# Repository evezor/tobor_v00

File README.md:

# tobor_v00
Tobor (robot spelled backwards), was built to be the most versatile open-source robotics system

Find out more about this project, additional source files will be released [here](https://www.crowdsupply.com/evezor-inc/tobor-robotics-and-automation-platform)

Tobor Robot Arm Features

* ESP32 microcontroller with 4 MB SPIRAM
    * Runs Micropython
* 3 DRV8825 stepper motor drivers
* 2 AS5048B 14-bit absolute encoders
    * Allows for low/no motion homing
    * Collaborative programming
* 8 position addressable LED ring
    * Can be used to display states of motors or the machine
* External stepper driver and peripheral port
* CNC controller powered by Fluid NC with dedicated FTDI and reset switch
* Micro-SD card slot
* WiFi enabled
* CANbus Edge Board Interface
* Servo header
* 24 VDC power input
* 1 user programmable tactile button
* Reset button
* FTDI port
* Edgeboard standards
    * Heartbeat LED
    * Function button
    * Status addressable LED

Find out more about this project, additional source files will be released [here](https://www.crowdsupply.com/evezor-inc/tobor-robotics-and-automation-platform)

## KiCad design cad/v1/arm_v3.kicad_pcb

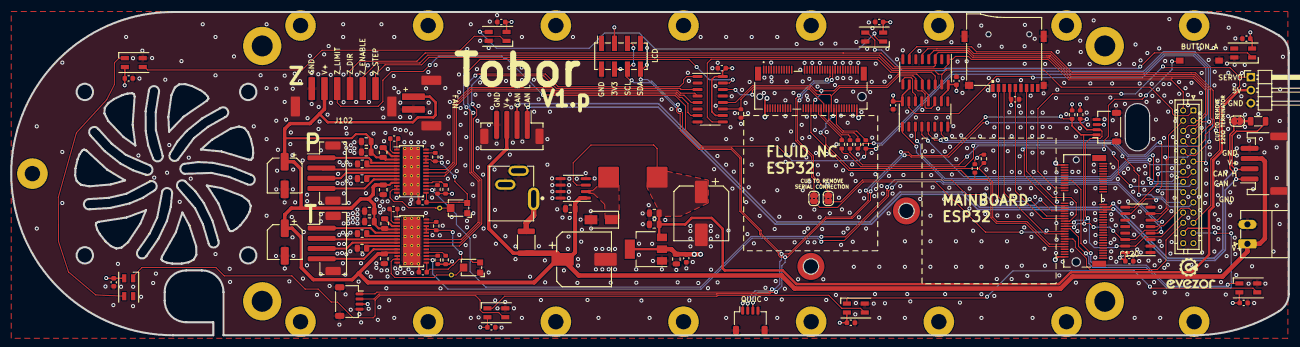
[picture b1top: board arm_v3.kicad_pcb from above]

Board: 4 copper layers, 250.2 x 63.3 mm, 121 parts (0 on the bottom side), 98 nets.

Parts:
C101, C102, C103, C104, C105, C106, C107, C108, C114, C116, C117, C118, C119, C120: .1uF; C_0603_1608Metric
C109, C111: 220uF; CP_Elec_10x10.5
C110, C112, C205, C305: 4.7uF 50V; C_0805_2012Metric
C113, C115: 22uF; C_0805_2012Metric
C201, C301: 10 nF; C_0603_1608Metric
C202, C302: 0.47uF; C_0603_1608Metric
C203, C206, C207, C303, C306, C307: .1uF 100V; C_0805_2012Metric
C204, C304: 47uF; CP_Elec_6.3x7.7
D101, D102, D103, D104, D105, D106, D107, D108: SK6812MINI; LED_SK6812MINI_PLCC4_3.5x3.5mm_P1.75mm
D109: SX35_SCHOTTKY; D_SMA
F101: Polyfuse_Small; Fuse_1812_4532Metric
H101, H102, H103, H104: MountingHole; MountingHole_4.1mm_M4_DIN965_Pad
H105, H106, H107, H108, H109, H110, H111, H112, H113, H114, H115, H116, H117, H118, H119, H120, H121: MountingHole; MountingHole_3mm_Pad
H122, H123: MountingHole; Mounting_Wuerth_WA-SMSI-M2_H2.5mm_9774025243
J101: Conn_01x03; PhoenixContact_MC_1,5_2-G-3.81_1x02_P3.81mm_Horizontal
J102: Conn_01x06_MountingPin; CONN_JST_XH_6_VERTICAL
J103: fan; JST_XH_2_VERTICAL
J104: Conn_01x03; PinHeader_1x03_P2.54mm_Horizontal
J105: Conn_02x04_Odd_Even; PinSocket_2x04_P2.54mm_Vertical_SMD
J106, J108, J110: Conn_01x04_MountingPin; JST_SH_SM04B-SRSS-TB_1x04-1MP_P1.00mm_Horizontal
J107: Barrel_Jack_Switch; Vertical_barrel
J109: Conn_02x10_Odd_Even; JST_PHD_B28B-PHDSS_2x14_P2.00mm_Vertical
J111: Micro_SD_Card_Det; Conn_uSDcard
J112: Conn_01x04; JST_PH_S4B-PH-SM4-TB_1x04-1MP_P2.00mm_Horizontal
J113: Conn_01x02; JST_PH_B4B-PH-SM4-TB_1x04-1MP_P2.00mm_Vertical
J114, J115: Bus_M.2_Socket_E_ESP32; AMPHENOL_MDT420E02002
J201, J301: Conn_01x04_MountingPin; JST_PH_B4B-PH-SM4-TB_1x04-1MP_P2.00mm_Vertical
JP101, JP102: SolderJumper_2_Bridged; SolderJumper-2_P1.3mm_Bridged2Bar_RoundedPad1.0x1.5mm
JP103: can_jumper; SolderJumper-2_P1.3mm_Bridged2Bar_RoundedPad1.0x1.5mm
L101: 68uF; INDUCTOR-68uH
R101, R102: 4.7k; R_0603_1608Metric
R103: 120R; R_1206_3216Metric
R104, R105, R106, R202, R203, R302, R303: 10k; R_0603_1608Metric
R107, R108, R109, R110: 220R; R_0603_1608Metric
R201, R301: 1.5k; R_0603_1608Metric
R204, R205, R304, R305: 0.1R; R_0805_2012Metric
RV201, RV301: 10k POT; Potentiometer_Bourns_TC33X_Vertical
SW101: SW_Push; SWITCH_2x3_SMD_TACTILE_GREEN
TP201, TP301: TestPoint; TestPoint_THTPad_D1.0mm_Drill0.5mm
U101: XL1509; SOIC-8_3.9x4.9mm_P1.27mm
U102: AMS1117-3.3; SOT-223-3_TabPin2
U103, U104, U105: 74AHCT595; SOIC-16_3.9x9.9mm_P1.27mm
U106: PCF8574; SOIC-16_3.9x9.9mm_P1.27mm
U201, U301: DRV8825PWPR; HTSSOP-28-1EP_4.4x9.7mm_P0.65mm_EP3.4x9.5mm_ThermalVias

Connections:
+3V3: C101.2, C102.2, C103.2, C104.2, C105.2, C106.2, C107.2, C108.2, C114.1, C115.1, C116.1, C117.2, C118.2, C119.2, C120.1, D101.4 (VDD), D102.4 (VDD), D103.4 (VDD), D104.4 (VDD), D105.4 (VDD), D106.4 (VDD), D107.4 (VDD), D108.4 (VDD), J105.3, J105.4, J106.3, J108.3, J109.27, J110.3, J111.4 (VDD), J114.2 (3.3V), J114.74 (3.3V), J115.2 (3.3V), J115.74 (3.3V), R101.1, R102.1, R104.2, R106.2, R201.2, R203.2, R301.2, R303.2, U102.2 (VO), U103.10 (~SRCLR), U103.16 (VCC), U104.10 (~SRCLR), U104.16 (VCC), U105.10 (~SRCLR), U105.16 (VCC), U106.16 (VDD)
+5V: C111.1, C112.1, C113.1, J104.2, J109.26, L101.1, U101.3 (FEEDBACK), U102.3 (VI)
+VDC: C109.1, C110.1, C203.1, C204.1, C205.1, C206.2, C207.2, C303.1, C304.1, C305.1, C306.2, C307.2, F101.1, J101.1, J102.5, J103.1, J112.3, J113.3, U101.1 (VIN), U201.4 (VMA), U201.11 (VMB), U301.4 (VMA), U301.11 (VMB)
/A_DIR: J109.8, U104.7 (QH)
/A_ENABLE: J109.7, U104.5 (QF)
/A_LIMIT: J109.10, R108.1
/A_RESET: J109.9, U106.7 (P3)
/A_STEP: J109.6, U104.4 (QE)
/BUTTON A: J114.34, SW101.1
/B_DIR: J109.13, U105.3 (QD)
/B_ENABLE: J109.12, U105.1 (QB)
/B_LIMIT: J109.15, R109.1
/B_RESET: J109.14, U106.9 (P4)
/B_STEP: J109.11, U105.15 (QA)
/CAN_H: J112.2, J113.2, J114.35 (CAN_H), R103.2
/CAN_L: J112.1, J113.1, J114.37 (CAN_L), JP103.2 (B)
/C_DIR: J109.18, U105.7 (QH)
/C_ENABLE: J109.17, U105.5 (QF)
/C_LIMIT: J109.20, R110.1
/C_RESET: J109.19, U106.10 (P5)
/C_STEP: J109.16, U105.4 (QE)
/GRBL_PROBE: J114.66, J115.38, R104.1
/GRBL_RX: J114.38, JP102.2 (B)
/GRBL_RXD0: J115.53 (UART_RX), JP101.1 (A)
/GRBL_TX: J114.54, JP101.2 (B)
/GRBL_TXDO: J115.55 (UART_TX), JP102.1 (A)
/HOLD: J114.64, J115.56, R106.1
/I2S_CLK: J115.54, R105.2, U103.11 (SRCLK), U104.11 (SRCLK), U105.11 (SRCLK)
/I2S_DATA: J115.48, U103.14 (SER)
/I2S_WS: J115.40, U103.12 (RCLK), U104.12 (RCLK), U105.12 (RCLK)
/NEO_RING: D101.3 (DIN), J114.14
/P25: J109.25, J114.52
/P60: J109.24, J114.60
/PHI_STEPPER/3VP: C302.1, R302.2, RV301.3, U301.15 (V3P3OUT), U301.24 (MODE0), U301.25 (MODE1), U301.26 (MODE2)
/SCK: J111.5 (CLK), J114.44
/SCL: J105.5, J105.6, J106.1, J108.1, J109.21, J110.1, J114.50, R101.2, U106.14 (SCL)
/SDA: J105.7, J105.8, J106.2, J108.2, J109.22, J110.2, J114.48, R102.2, U106.15 (SDA)
/SD_CS: J111.2 (DAT3/CD), J114.42
/SD_MISO: J111.7 (DAT0), J114.46
/SD_MOSI: J111.3 (CMD), J114.56
/SERVO: J104.1, J109.23, J114.20
/THETA_STEPPER/3VP: C202.1, R202.2, RV201.3, U201.15 (V3P3OUT), U201.24 (MODE0), U201.25 (MODE1), U201.26 (MODE2)
/Z_DIR: J102.3, J109.3, U104.3 (QD)
/Z_ENABLE: J102.2, J109.2, U104.1 (QB)
/Z_LIMIT: J102.4, J109.5, R107.1
/Z_RESET: J109.4, U106.6 (P2)
/Z_STEP: J102.1, J109.1, U104.15 (QA)
GND: C101.1, C102.1, C103.1, C104.1, C105.1, C106.1, C107.1, C108.1, C109.2, C110.2, C111.2, C112.2, C113.2, C114.2, C115.2, C116.2, C117.1, C118.1, C119.1, C120.2, C202.2, C204.2, C205.2, C206.1, C207.1, C302.2, C304.2, C305.2, C306.1, C307.1, D101.2 (VSS), D102.2 (VSS), D103.2 (VSS), D105.2 (VSS), D106.2 (VSS), D107.2 (VSS), D108.2 (VSS), D109.2 (A), J101.2, J102.6, J102.MP (MountPin), J103.2, J103.MP (MountPin), J104.3, J105.1, J105.2, J106.4, J106.MP (MountPin), J107.2, J107.3, J108.4, J108.MP (MountPin), J109.28, J110.4, J110.MP (MountPin), J111.6 (VSS), J111.11 (SHIELD), J112.4, J112.MP (MountPin), J113.4, J113.MP (MountPin), J114.1 (GND), J114.7 (GND), J114.18 (GND), J114.33 (GND), J114.36 (GND), J114.39 (GND), J114.45 (GND), J114.57 (GND), J114.63 (GND), J114.69 (GND), J114.75 (GND), J115.1 (GND), J115.7 (GND), J115.18 (GND), J115.33 (GND), J115.36 (GND), J115.39 (GND), J115.45 (GND), J115.57 (GND), J115.63 (GND), J115.69 (GND), J115.75 (GND), J201.MP (MountPin), J301.MP (MountPin), R105.1, R204.1, R205.1, R304.1, R305.1, RV201.1, RV301.1, SW101.2, U101.4 (ON/OFF), U101.5 (GND), U101.6 (GND), U101.7 (GND), U101.8 (GND), U102.1 (GND), U103.8 (GND), U103.13 (~OE), U104.8 (GND), U104.13 (~OE), U105.8 (GND), U105.13 (~OE), U106.1 (A0), U106.2 (A1), U106.3 (A2), U106.8 (VSS), U201.14 (GND), U201.28 (GND), U201.29 (GND), U301.14 (GND), U301.28 (GND), U301.29 (GND)
unnamed: D101.1 (DOUT), D102.3 (DIN)
unnamed: D102.1 (DOUT), D103.3 (DIN)
unnamed: D103.1 (DOUT), D104.3 (DIN)
unnamed: D104.1 (DOUT), D105.3 (DIN)
unnamed: D105.1 (DOUT), D106.3 (DIN)
unnamed: D106.1 (DOUT), D107.3 (DIN)
unnamed: D107.1 (DOUT), D108.3 (DIN)
unnamed: D109.1 (K), L101.2, U101.2 (OUTPUT)
unnamed: F101.2, J107.1
unnamed: J115.44, R110.2
unnamed: J115.46, R109.2
unnamed: J115.52, R108.2
unnamed: J115.58, R107.2
unnamed: J201.1, U201.5 (AOUT1)
unnamed: J201.2, U201.7 (AOUT2)
unnamed: J201.3, U201.8 (BOUT2)
unnamed: J201.4, U201.10 (BOUT1)
unnamed: J301.1, U301.5 (AOUT1)
unnamed: J301.2, U301.7 (AOUT2)
unnamed: J301.3, U301.8 (BOUT2)
unnamed: J301.4, U301.10 (BOUT1)
unnamed: JP103.1 (A), R103.1
unnamed: U103.9 (QH'), U104.14 (SER)
unnamed: U104.9 (QH'), U105.14 (SER)
unnamed: R201.1, U201.18 (!FAULT)
unnamed: R202.1, U201.27 (!HOME)
unnamed: R203.1, U201.17 (!SLEEP)
unnamed: RV201.2, TP201.1, U201.12 (AVREF), U201.13 (BVREF)
unnamed: C201.1, U201.1 (CP1)
unnamed: C201.2, U201.2 (CP2)
unnamed: R205.2, U201.6 (ISENA)
unnamed: R204.2, U201.9 (ISENB)
unnamed: C203.2, U201.3 (VCP)
unnamed: R301.1, U301.18 (!FAULT)
unnamed: R302.1, U301.27 (!HOME)
unnamed: R303.1, U301.17 (!SLEEP)
unnamed: RV301.2, TP301.1, U301.12 (AVREF), U301.13 (BVREF)
unnamed: C301.1, U301.1 (CP1)
unnamed: C301.2, U301.2 (CP2)
unnamed: R305.2, U301.6 (ISENA)
unnamed: R304.2, U301.9 (ISENB)
unnamed: C303.2, U301.3 (VCP)
PHI_DIR: U103.7 (QH), U301.20 (DIR)
PHI_ENABLE: U103.5 (QF), U301.21 (!ENBL)
PHI_RESET: U106.5 (P1), U301.16 (!RESET)
PHI_STEP: U103.4 (QE), U301.22 (STEP)
THETA_DIR: U103.3 (QD), U201.20 (DIR)
THETA_ENABLE: U103.1 (QB), U201.21 (!ENBL)
THETA_RESET: U106.4 (P0), U201.16 (!RESET)
THETA_STEP: U103.15 (QA), U201.22 (STEP)

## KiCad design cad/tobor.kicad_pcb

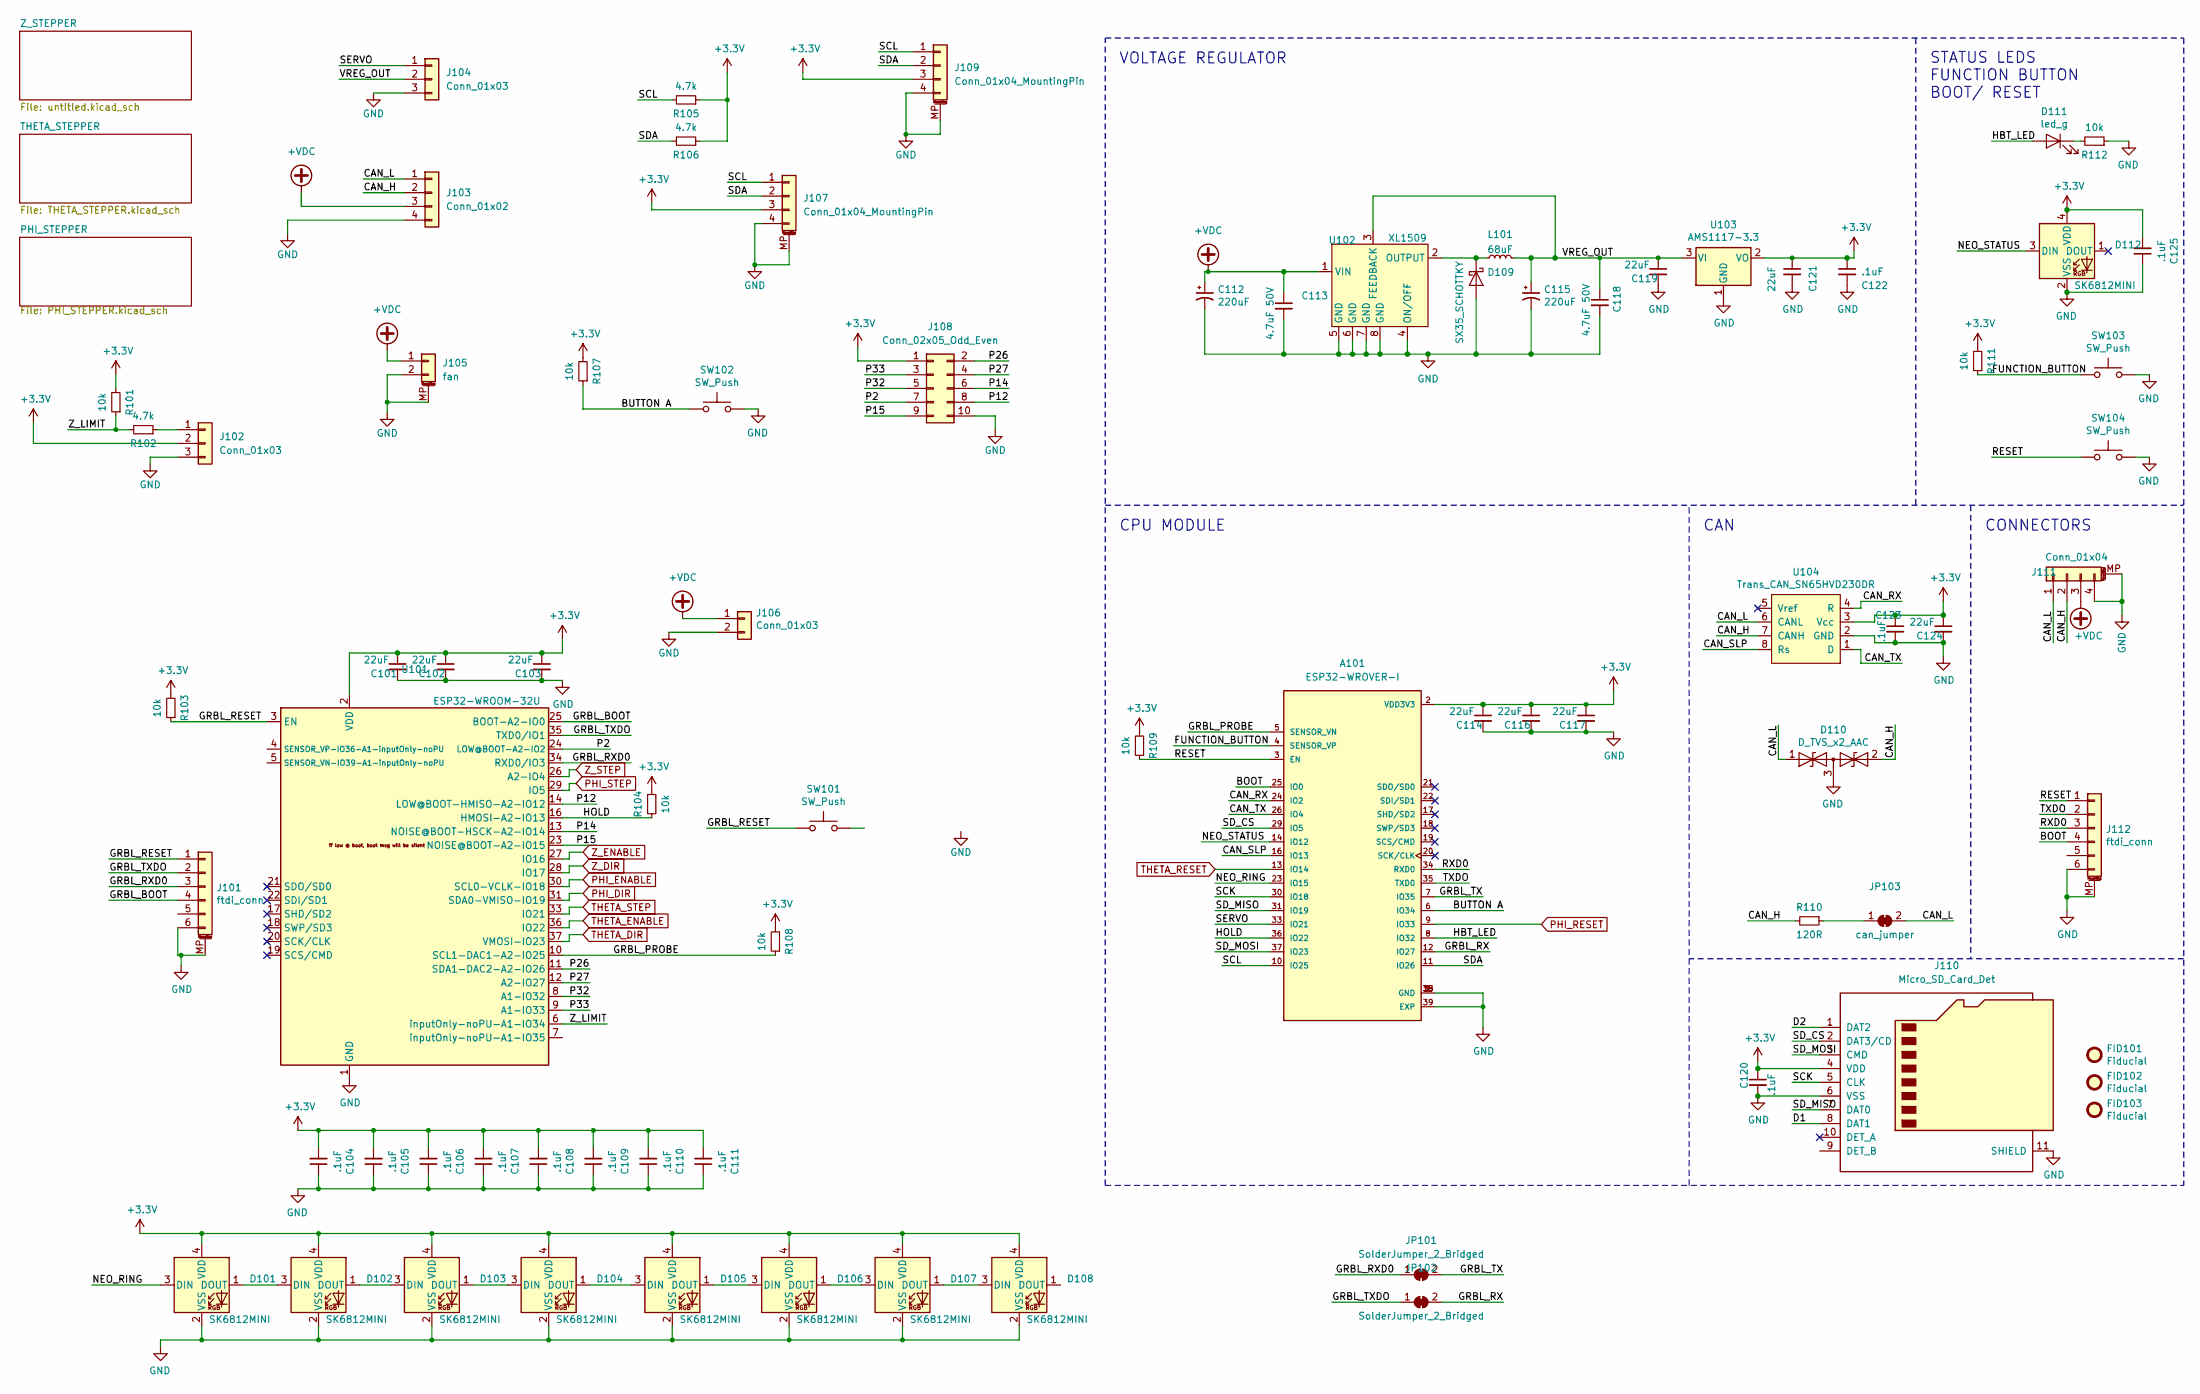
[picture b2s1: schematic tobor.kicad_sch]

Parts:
A101: ESP32-WROVER-I; XCVR_ESP32-WROVER-I; DIGI-KEY_PART_NUMBER 1904-1008-1-ND
C101, C102, C103, C114, C116, C117, C119, C121, C124: 22uF; C_0805_2012Metric
C104, C105, C106, C107, C108, C109, C110, C111, C120, C122, C123, C125: .1uF; C_0603_1608Metric
C112, C115: 220uF; CP_Elec_10x10.5
C113, C118: 4.7uF 50V; C_0805_2012Metric
D101, D102, D103, D104, D105, D106, D107, D108, D112: SK6812MINI; LED_SK6812MINI_PLCC4_3.5x3.5mm_P1.75mm
D109: SX35_SCHOTTKY; D_SMA
D110: D_TVS_x2_AAC; SOT-23
D111: led_g; LED_0603_1608Metric
FID101, FID102, FID103: Fiducial; Fiducial_0.5mm_Mask1mm
J101, J112: ftdi_conn; JST_SH_BM06B-SRSS-TB_1x06-1MP_P1.00mm_Vertical
J102: Conn_01x03; JST_PH_B3B-PH-SM4-TB_1x03-1MP_P2.00mm_Vertical
J103: Conn_01x02; PhoenixContact_MCV_1,5_4-GF-3.81_1x04_P3.81mm_Vertical_Thre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
J104: Conn_01x03; PinHeader_1x03_P2.54mm_Horizontal
J105: fan; JST_XH_2_VERTICAL
J106: Conn_01x03; PhoenixContact_MC_1,5_2-G-3.81_1x02_P3.81mm_Horizontal
J107, J109: Conn_01x04_MountingPin; JST_SH_SM04B-SRSS-TB_1x04-1MP_P1.00mm_Horizontal
J108: Conn_02x05_Odd_Even; IDC-Header_2x05_P2.54mm_Vertical
J110: Micro_SD_Card_Det; Conn_uSDcard
J111: Conn_01x04; JST_PH_S4B-PH-SM4-TB_1x04-1MP_P2.00mm_Horizontal
JP101, JP102: SolderJumper_2_Bridged; SolderJumper-2_P1.3mm_Bridged2Bar_RoundedPad1.0x1.5mm
JP103: can_jumper; SolderJumper-2_P1.3mm_Bridged2Bar_RoundedPad1.0x1.5mm
L101: 68uF; INDUCTOR-68uH
R101, R103, R104, R107, R108, R109, R111, R112: 10k; R_0603_1608Metric
R102, R105, R106: 4.7k; R_0603_1608Metric
R110: 120R; R_1206_3216Metric
SW101, SW102, SW103, SW104: SW_Push; SWITCH_2x3_SMD_TACTILE_GREEN
U101: ESP32-WROOM-32U; ESP32-WROOM-32U_evezor
U102: XL1509; SOIC-8_3.9x4.9mm_P1.27mm
U103: AMS1117-3.3; SOT-223-3_TabPin2
U104: Trans_CAN_SN65HVD230DR; CAN-TRANS-SN65HVD230DR

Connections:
+3V3: A101.2 (VDD3V3), C101.1, C102.1, C103.1, C104.2, C105.2, C106.2, C107.2, C108.2, C109.2, C110.2, C111.2, C114.1, C116.1, C117.1, C120.1, C121.1, C122.1, C123.1, C124.1, C125.2, D101.4 (VDD), D102.4 (VDD), D103.4 (VDD), D104.4 (VDD), D105.4 (VDD), D106.4 (VDD), D107.4 (VDD), D108.4 (VDD), D112.4 (VDD), J102.2, J107.3, J108.1, J109.3, J110.4 (VDD), R101.2, R103.2, R104.1, R105.1, R106.1, R107.2, R108.2, R109.2, R111.2, U101.2 (VDD), U103.2 (VO), U104.3 (Vcc); also elsewhere on the board
+VDC: C112.1, C113.1, J103.3, J105.1, J106.1, J111.3, U102.1 (VIN); also elsewhere on the board
/BOOT: A101.25 (IO0), J112.4
/BUTTON A: A101.6 (IO34), R107.1, SW102.1
/CAN_H: D110.2 (A2), J103.2, J111.2, R110.2, U104.7 (CANH)
/CAN_L: D110.1 (A1), J103.1, J111.1, JP103.2 (B), U104.6 (CANL)
/CAN_RX: A101.24 (IO2), U104.4 (R)
/CAN_SLP: A101.16 (IO13), U104.8 (Rs)
/CAN_TX: A101.26 (IO4), U104.1 (D)
/D1: J110.8 (DAT1)
/D2: J110.1 (DAT2)
/FUNCTION_BUTTON: A101.4 (SENSOR_VP), R111.1, SW103.1
/GRBL_BOOT: J101.4, U101.25 (BOOT-A2-IO0)
/GRBL_PROBE: A101.5 (SENSOR_VN), R108.1, U101.10 (SCL1-DAC1-A2-IO25)
/GRBL_RESET: J101.1, R103.1, SW101.1, U101.3 (EN)
/GRBL_RX: A101.12 (IO27), JP102.2 (B)
/GRBL_RXD0: J101.3, JP101.1 (A), U101.34 (RXD0/IO3)
/GRBL_TX: A101.7 (IO35), JP101.2 (B)
/GRBL_TXDO: J101.2, JP102.1 (A), U101.35 (TXD0/IO1)
/HBT_LED: A101.8 (IO32), D111.2 (A)
/HOLD: A101.36 (IO22), R104.2, U101.16 (HMOSI-A2-IO13)
/NEO_RING: A101.23 (IO15), D101.3 (DIN)
/NEO_STATUS: A101.14 (IO12), D112.3 (DIN)
/P2: J108.7, U101.24 (LOW@BOOT-A2-IO2)
/P12: J108.8, U101.14 (LOW@BOOT-HMISO-A2-IO12)
/P14: J108.6, U101.13 (NOISE@BOOT-HSCK-A2-IO14)
/P15: J108.9, U101.23 (NOISE@BOOT-A2-IO15)
/P26: J108.2, U101.11 (SDA1-DAC2-A2-IO26)
/P27: J108.4, U101.12 (A2-IO27)
/P32: J108.5, U101.8 (A1-IO32)
/P33: J108.3, U101.9 (A1-IO33)
/RESET: A101.3 (EN), J112.1, R109.1, SW104.1
/RXD0: A101.34 (RXD0), J112.3
/SCK: A101.30 (IO18), J110.5 (CLK)
/SCL: A101.10 (IO25), J107.1, J109.1, R105.2
/SDA: A101.11 (IO26), J107.2, J109.2, R106.2
/SD_CS: A101.29 (IO5), J110.2 (DAT3/CD)
/SD_MISO: A101.31 (IO19), J110.7 (DAT0)
/SD_MOSI: A101.37 (IO23), J110.3 (CMD)
/SERVO: A101.33 (IO21), J104.1
/TXDO: A101.35 (TXD0), J112.2
/VREG_OUT: C115.1, C118.1, C119.1, J104.2, L101.1, U102.3 (FEEDBACK), U103.3 (VI)
/Z_LIMIT: R101.1, R102.2, U101.6 (inputOnly-noPU-A1-IO34)
GND: A101.1 (GND), A101.15 (GND), A101.38 (GND), A101.39 (EXP), C101.2, C102.2, C103.2, C104.1, C105.1, C106.1, C107.1, C108.1, C109.1, C110.1, C111.1, C112.2, C113.2, C114.2, C115.2, C116.2, C117.2, C118.2, C119.2, C120.2, C121.2, C122.2, C123.2, C124.2, C125.1, D101.2 (VSS), D102.2 (VSS), D103.2 (VSS), D104.2 (VSS), D105.2 (VSS), D106.2 (VSS), D107.2 (VSS), D108.2 (VSS), D109.2 (A), D110.3 (common), D112.2 (VSS), J101.6, J101.MP (MountPin), J102.3, J103.4, J104.3, J105.2, J105.MP (MountPin), J106.2, J107.4, J107.MP (MountPin), J108.10, J109.4, J109.MP (MountPin), J110.6 (VSS), J110.11 (SHIELD), J111.4, J111.MP (MountPin), J112.6, J112.MP (MountPin), R112.1, SW101.2, SW102.2, SW103.2, SW104.2, U101.1 (GND), U101.15 (GND), U101.38 (GND), U101.39 (GND), U102.4 (ON/OFF), U102.5 (GND), U102.6 (GND), U102.7 (GND), U102.8 (GND), U103.1 (GND), U104.2 (GND); also elsewhere on the board
unnamed: D101.1 (DOUT), D102.3 (DIN)
unnamed: D102.1 (DOUT), D103.3 (DIN)
unnamed: D103.1 (DOUT), D104.3 (DIN)
unnamed: D104.1 (DOUT), D105.3 (DIN)
unnamed: D105.1 (DOUT), D106.3 (DIN)
unnamed: D106.1 (DOUT), D107.3 (DIN)
unnamed: D107.1 (DOUT), D108.3 (DIN)
unnamed: D109.1 (K), L101.2, U102.2 (OUTPUT)
unnamed: D111.1 (K), R112.2
unnamed: J102.1, R102.1
unnamed: JP103.1 (A), R110.1
PHI_DIR: U101.31 (SDA0-VMISO-IO19); also elsewhere on the board
PHI_ENABLE: U101.30 (SCL0-VCLK-IO18); also elsewhere on the board
PHI_RESET: A101.9 (IO33); also elsewhere on the board
PHI_STEP: U101.29 (IO5); also elsewhere on the board
THETA_DIR: U101.37 (VMOSI-IO23); also elsewhere on the board
THETA_ENABLE: U101.36 (IO22); also elsewhere on the board
THETA_RESET: A101.13 (IO14); also elsewhere on the board
THETA_STEP: U101.33 (IO21); also elsewhere on the board
Z_DIR: U101.28 (IO17); also elsewhere on the board
Z_ENABLE: U101.27 (IO16); also elsewhere on the board
Z_STEP: U101.26 (A2-IO4); also elsewhere on the board

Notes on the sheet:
VOLTAGE REGULATOR
CPU MODULE
CAN
STATUS LEDS FUNCTION BUTTON BOOT/ RESET
CONNECTORS

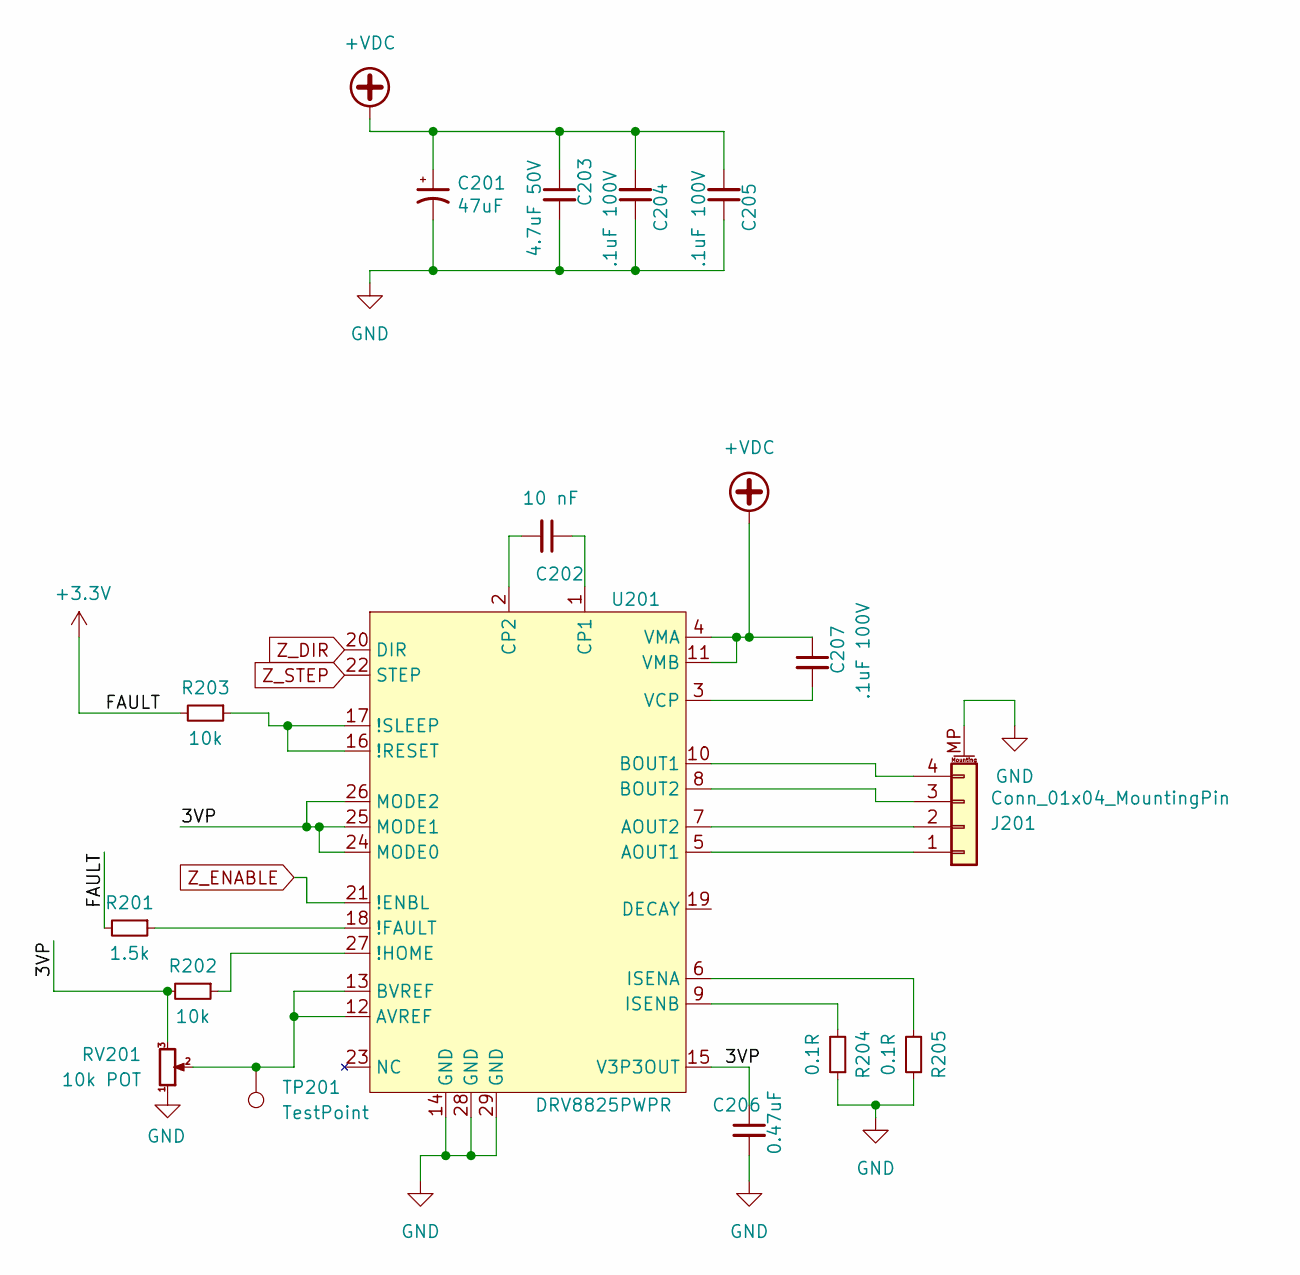
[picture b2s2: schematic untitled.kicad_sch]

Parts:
C201: 47uF; CP_Elec_6.3x7.7
C202: 10 nF; C_0603_1608Metric
C203: 4.7uF 50V; C_0805_2012Metric
C204, C205, C207: .1uF 100V; C_0805_2012Metric
C206: 0.47uF; C_0603_1608Metric
J201: Conn_01x04_MountingPin; JST_PH_B4B-PH-SM4-TB_1x04-1MP_P2.00mm_Vertical
R201: 1.5k; R_0603_1608Metric
R202, R203: 10k; R_0603_1608Metric
R204, R205: 0.1R; R_0805_2012Metric
RV201: 10k POT; Potentiometer_Bourns_TC33X_Vertical
TP201: TestPoint; TestPoint_THTPad_D1.0mm_Drill0.5mm
U201: DRV8825PWPR; HTSSOP-28-1EP_4.4x9.7mm_P0.65mm_EP3.4x9.5mm_ThermalVias

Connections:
+3V3: R201.2, R203.2; also elsewhere on the board
+VDC: C201.1, C203.1, C204.2, C205.2, C207.1, U201.4 (VMA), U201.11 (VMB); also elsewhere on the board
/Z_STEPPER/3VP: C206.1, R202.2, RV201.3, U201.15 (V3P3OUT), U201.24 (MODE0), U201.25 (MODE1), U201.26 (MODE2)
GND: C201.2, C203.2, C204.1, C205.1, C206.2, J201.MP (MountPin), R204.1, R205.1, RV201.1, U201.14 (GND), U201.28 (GND), U201.29 (GND); also elsewhere on the board
unnamed: J201.1, U201.5 (AOUT1)
unnamed: J201.2, U201.7 (AOUT2)
unnamed: J201.3, U201.8 (BOUT2)
unnamed: J201.4, U201.10 (BOUT1)
unnamed: R201.1, U201.18 (!FAULT)
unnamed: R202.1, U201.27 (!HOME)
unnamed: R203.1, U201.16 (!RESET), U201.17 (!SLEEP)
unnamed: RV201.2, TP201.1, U201.12 (AVREF), U201.13 (BVREF)
unnamed: C202.1, U201.1 (CP1)
unnamed: C202.2, U201.2 (CP2)
unnamed: R205.2, U201.6 (ISENA)
unnamed: R204.2, U201.9 (ISENB)
unnamed: C207.2, U201.3 (VCP)
Z_DIR: U201.20 (DIR); also elsewhere on the board
Z_ENABLE: U201.21 (!ENBL); also elsewhere on the board
Z_STEP: U201.22 (STEP); also elsewhere on the board

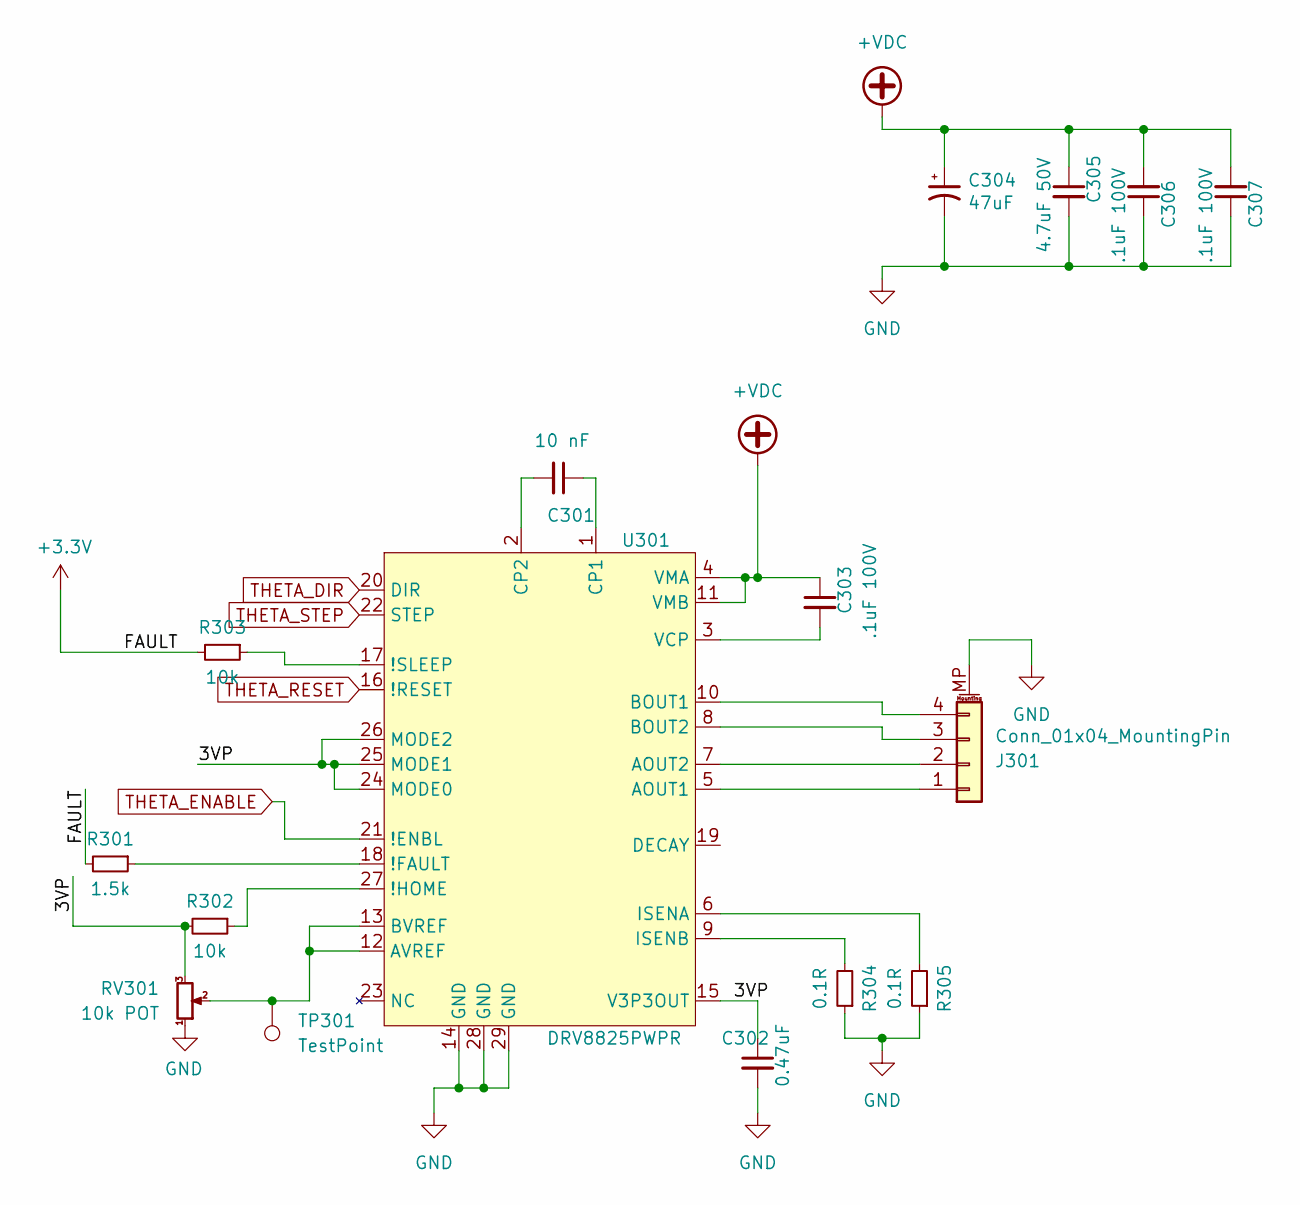
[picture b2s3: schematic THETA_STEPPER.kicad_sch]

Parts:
C301: 10 nF; C_0603_1608Metric
C302: 0.47uF; C_0603_1608Metric
C303, C306, C307: .1uF 100V; C_0805_2012Metric
C304: 47uF; CP_Elec_6.3x7.7
C305: 4.7uF 50V; C_0805_2012Metric
J301: Conn_01x04_MountingPin; JST_PH_B4B-PH-SM4-TB_1x04-1MP_P2.00mm_Vertical
R301: 1.5k; R_0603_1608Metric
R302, R303: 10k; R_0603_1608Metric
R304, R305: 0.1R; R_0805_2012Metric
RV301: 10k POT; Potentiometer_Bourns_TC33X_Vertical
TP301: TestPoint; TestPoint_THTPad_D1.0mm_Drill0.5mm
U301: DRV8825PWPR; HTSSOP-28-1EP_4.4x9.7mm_P0.65mm_EP3.4x9.5mm_ThermalVias

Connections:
+3V3: R301.2, R303.2; also elsewhere on the board
+VDC: C303.1, C304.1, C305.1, C306.2, C307.2, U301.4 (VMA), U301.11 (VMB); also elsewhere on the board
/THETA_STEPPER/3VP: C302.1, R302.2, RV301.3, U301.15 (V3P3OUT), U301.24 (MODE0), U301.25 (MODE1), U301.26 (MODE2)
GND: C302.2, C304.2, C305.2, C306.1, C307.1, J301.MP (MountPin), R304.1, R305.1, RV301.1, U301.14 (GND), U301.28 (GND), U301.29 (GND); also elsewhere on the board
unnamed: J301.1, U301.5 (AOUT1)
unnamed: J301.2, U301.7 (AOUT2)
unnamed: J301.3, U301.8 (BOUT2)
unnamed: J301.4, U301.10 (BOUT1)
unnamed: R301.1, U301.18 (!FAULT)
unnamed: R302.1, U301.27 (!HOME)
unnamed: R303.1, U301.17 (!SLEEP)
unnamed: RV301.2, TP301.1, U301.12 (AVREF), U301.13 (BVREF)
unnamed: C301.1, U301.1 (CP1)
unnamed: C301.2, U301.2 (CP2)
unnamed: R305.2, U301.6 (ISENA)
unnamed: R304.2, U301.9 (ISENB)
unnamed: C303.2, U301.3 (VCP)
THETA_DIR: U301.20 (DIR); also elsewhere on the board
THETA_ENABLE: U301.21 (!ENBL); also elsewhere on the board
THETA_RESET: U301.16 (!RESET); also elsewhere on the board
THETA_STEP: U301.22 (STEP); also elsewhere on the board

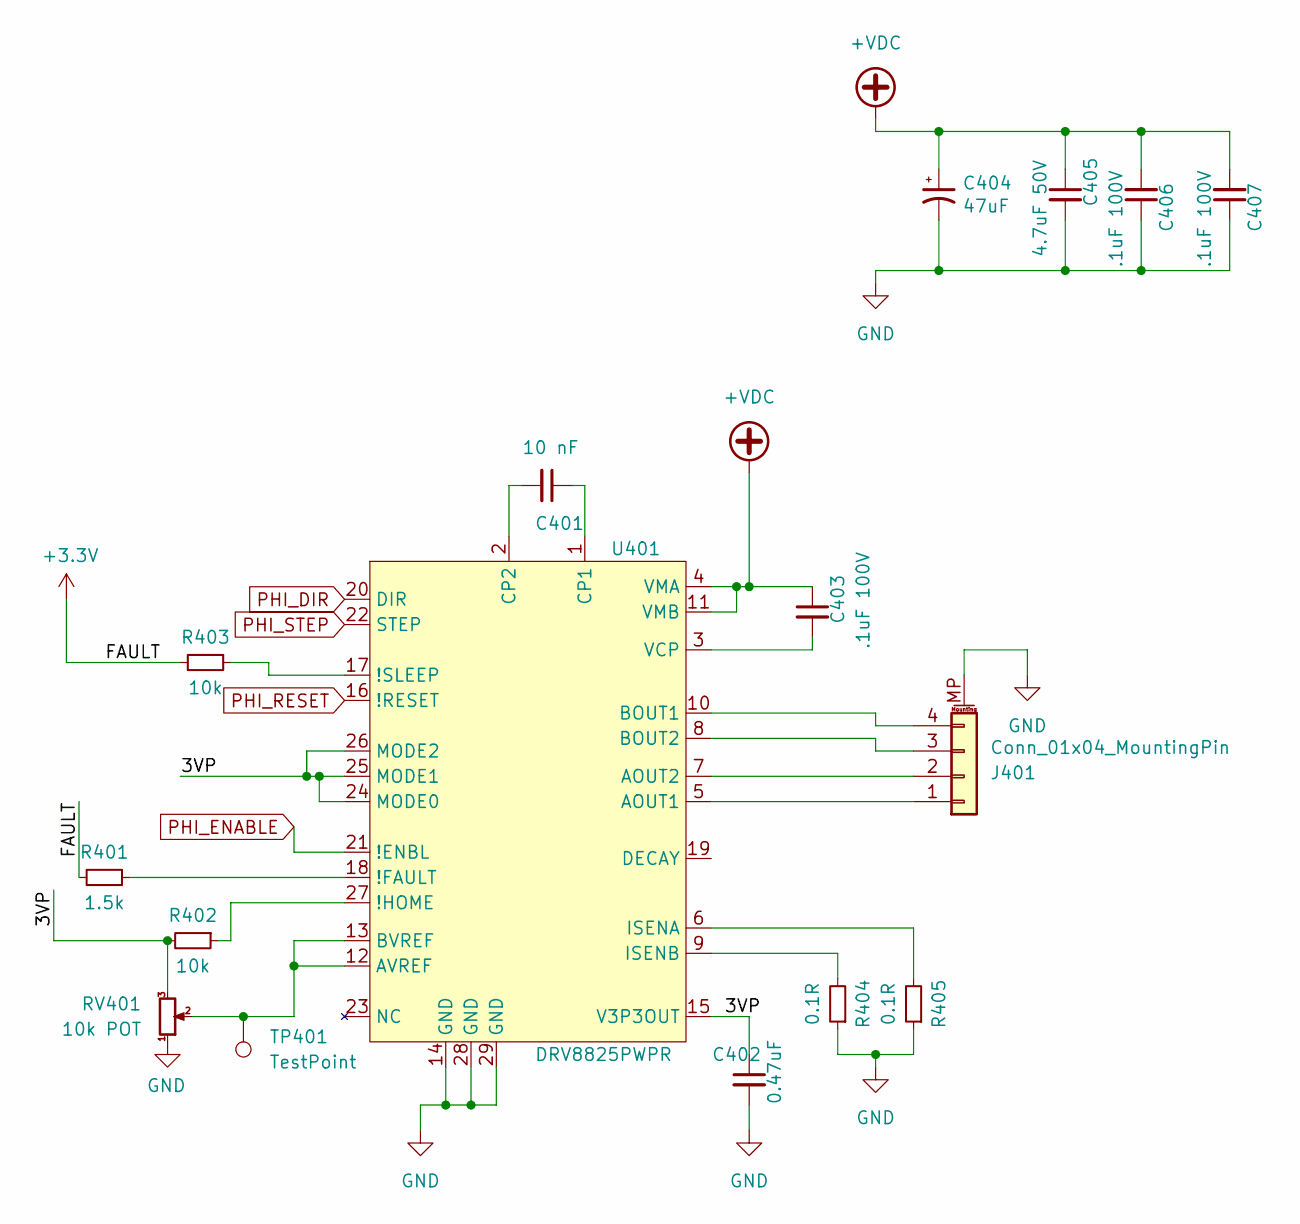
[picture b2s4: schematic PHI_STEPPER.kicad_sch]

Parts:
C401: 10 nF; C_0603_1608Metric
C402: 0.47uF; C_0603_1608Metric
C403, C406, C407: .1uF 100V; C_0805_2012Metric
C404: 47uF; CP_Elec_6.3x7.7
C405: 4.7uF 50V; C_0805_2012Metric
J401: Conn_01x04_MountingPin; JST_PH_B4B-PH-SM4-TB_1x04-1MP_P2.00mm_Vertical
R401: 1.5k; R_0603_1608Metric
R402, R403: 10k; R_0603_1608Metric
R404, R405: 0.1R; R_0805_2012Metric
RV401: 10k POT; Potentiometer_Bourns_TC33X_Vertical
TP401: TestPoint; TestPoint_THTPad_D1.0mm_Drill0.5mm
U401: DRV8825PWPR; HTSSOP-28-1EP_4.4x9.7mm_P0.65mm_EP3.4x9.5mm_ThermalVias

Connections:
+3V3: R401.2, R403.2; also elsewhere on the board
+VDC: C403.1, C404.1, C405.1, C406.2, C407.2, U401.4 (VMA), U401.11 (VMB); also elsewhere on the board
/PHI_STEPPER/3VP: C402.1, R402.2, RV401.3, U401.15 (V3P3OUT), U401.24 (MODE0), U401.25 (MODE1), U401.26 (MODE2)
GND: C402.2, C404.2, C405.2, C406.1, C407.1, J401.MP (MountPin), R404.1, R405.1, RV401.1, U401.14 (GND), U401.28 (GND), U401.29 (GND); also elsewhere on the board
unnamed: J401.1, U401.5 (AOUT1)
unnamed: J401.2, U401.7 (AOUT2)
unnamed: J401.3, U401.8 (BOUT2)
unnamed: J401.4, U401.10 (BOUT1)
unnamed: R401.1, U401.18 (!FAULT)
unnamed: R402.1, U401.27 (!HOME)
unnamed: R403.1, U401.17 (!SLEEP)
unnamed: RV401.2, TP401.1, U401.12 (AVREF), U401.13 (BVREF)
unnamed: C401.1, U401.1 (CP1)
unnamed: C401.2, U401.2 (CP2)
unnamed: R405.2, U401.6 (ISENA)
unnamed: R404.2, U401.9 (ISENB)
unnamed: C403.2, U401.3 (VCP)
PHI_DIR: U401.20 (DIR); also elsewhere on the board
PHI_ENABLE: U401.21 (!ENBL); also elsewhere on the board
PHI_RESET: U401.16 (!RESET); also elsewhere on the board
PHI_STEP: U401.22 (STEP); also elsewhere on the board

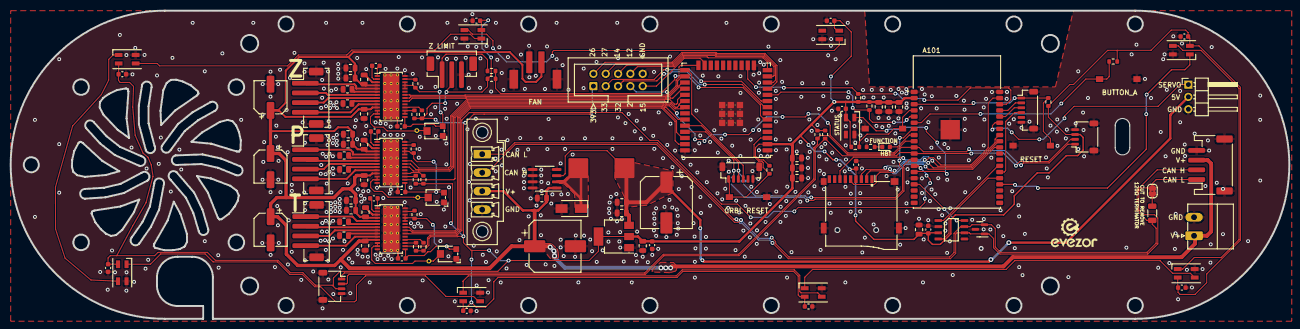
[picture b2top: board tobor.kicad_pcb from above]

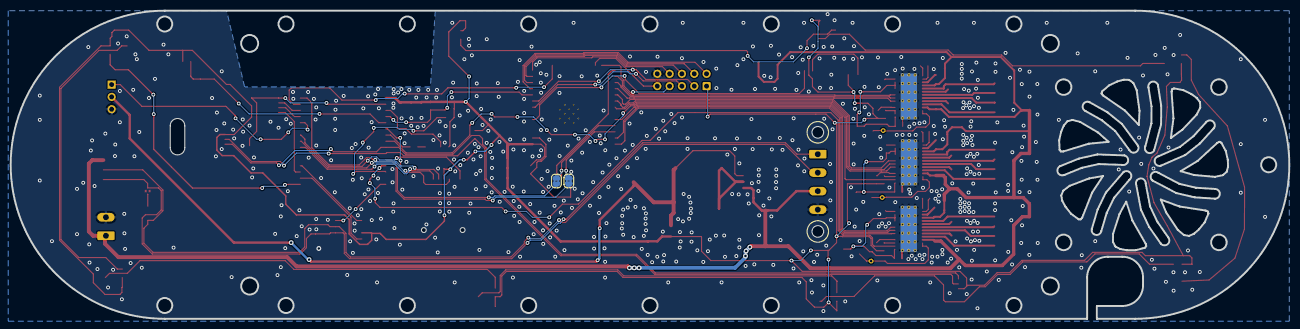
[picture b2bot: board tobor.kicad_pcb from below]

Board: 2 copper layers, 263.5 x 63.5 mm, 122 parts (2 on the bottom side), 106 nets.

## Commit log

2024-10-14 init
2024-10-14 add example penplotter firmware
2025-03-23 add v1
